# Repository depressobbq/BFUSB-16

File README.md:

# BFUSB-16
its a Big effin USB hub, based on off the shelf parts.

The goal here is to have something with easy to source parts, that asre simultaniously as easy to solder by hand as possible. I went with good ol barrel caps, and single stacked usbs. Also I went with crystals at each of the hub chips, despite them being able to run without one, just due to no trusting it to actually do so. the hope here being that with nice big beefy caps and crystals on each hub chip, this thing ought to be stable even fully populated.
If it works as intended, it should be great for people like me who need a million USB's hooked to their PC for sim racing, but it would also be cool to see if it would work as a 16 USB RAID0 (if my numbers are correct your average flashdrive * 16 is the full usb 2 bandwidth)
Any comments / questions, leave them in the issues, and if you want to help improve the design make a pull request. Im usually not far from a keyboard. This PCB should be good to go with either JLCPCB ( my favorite) or PCBWay.

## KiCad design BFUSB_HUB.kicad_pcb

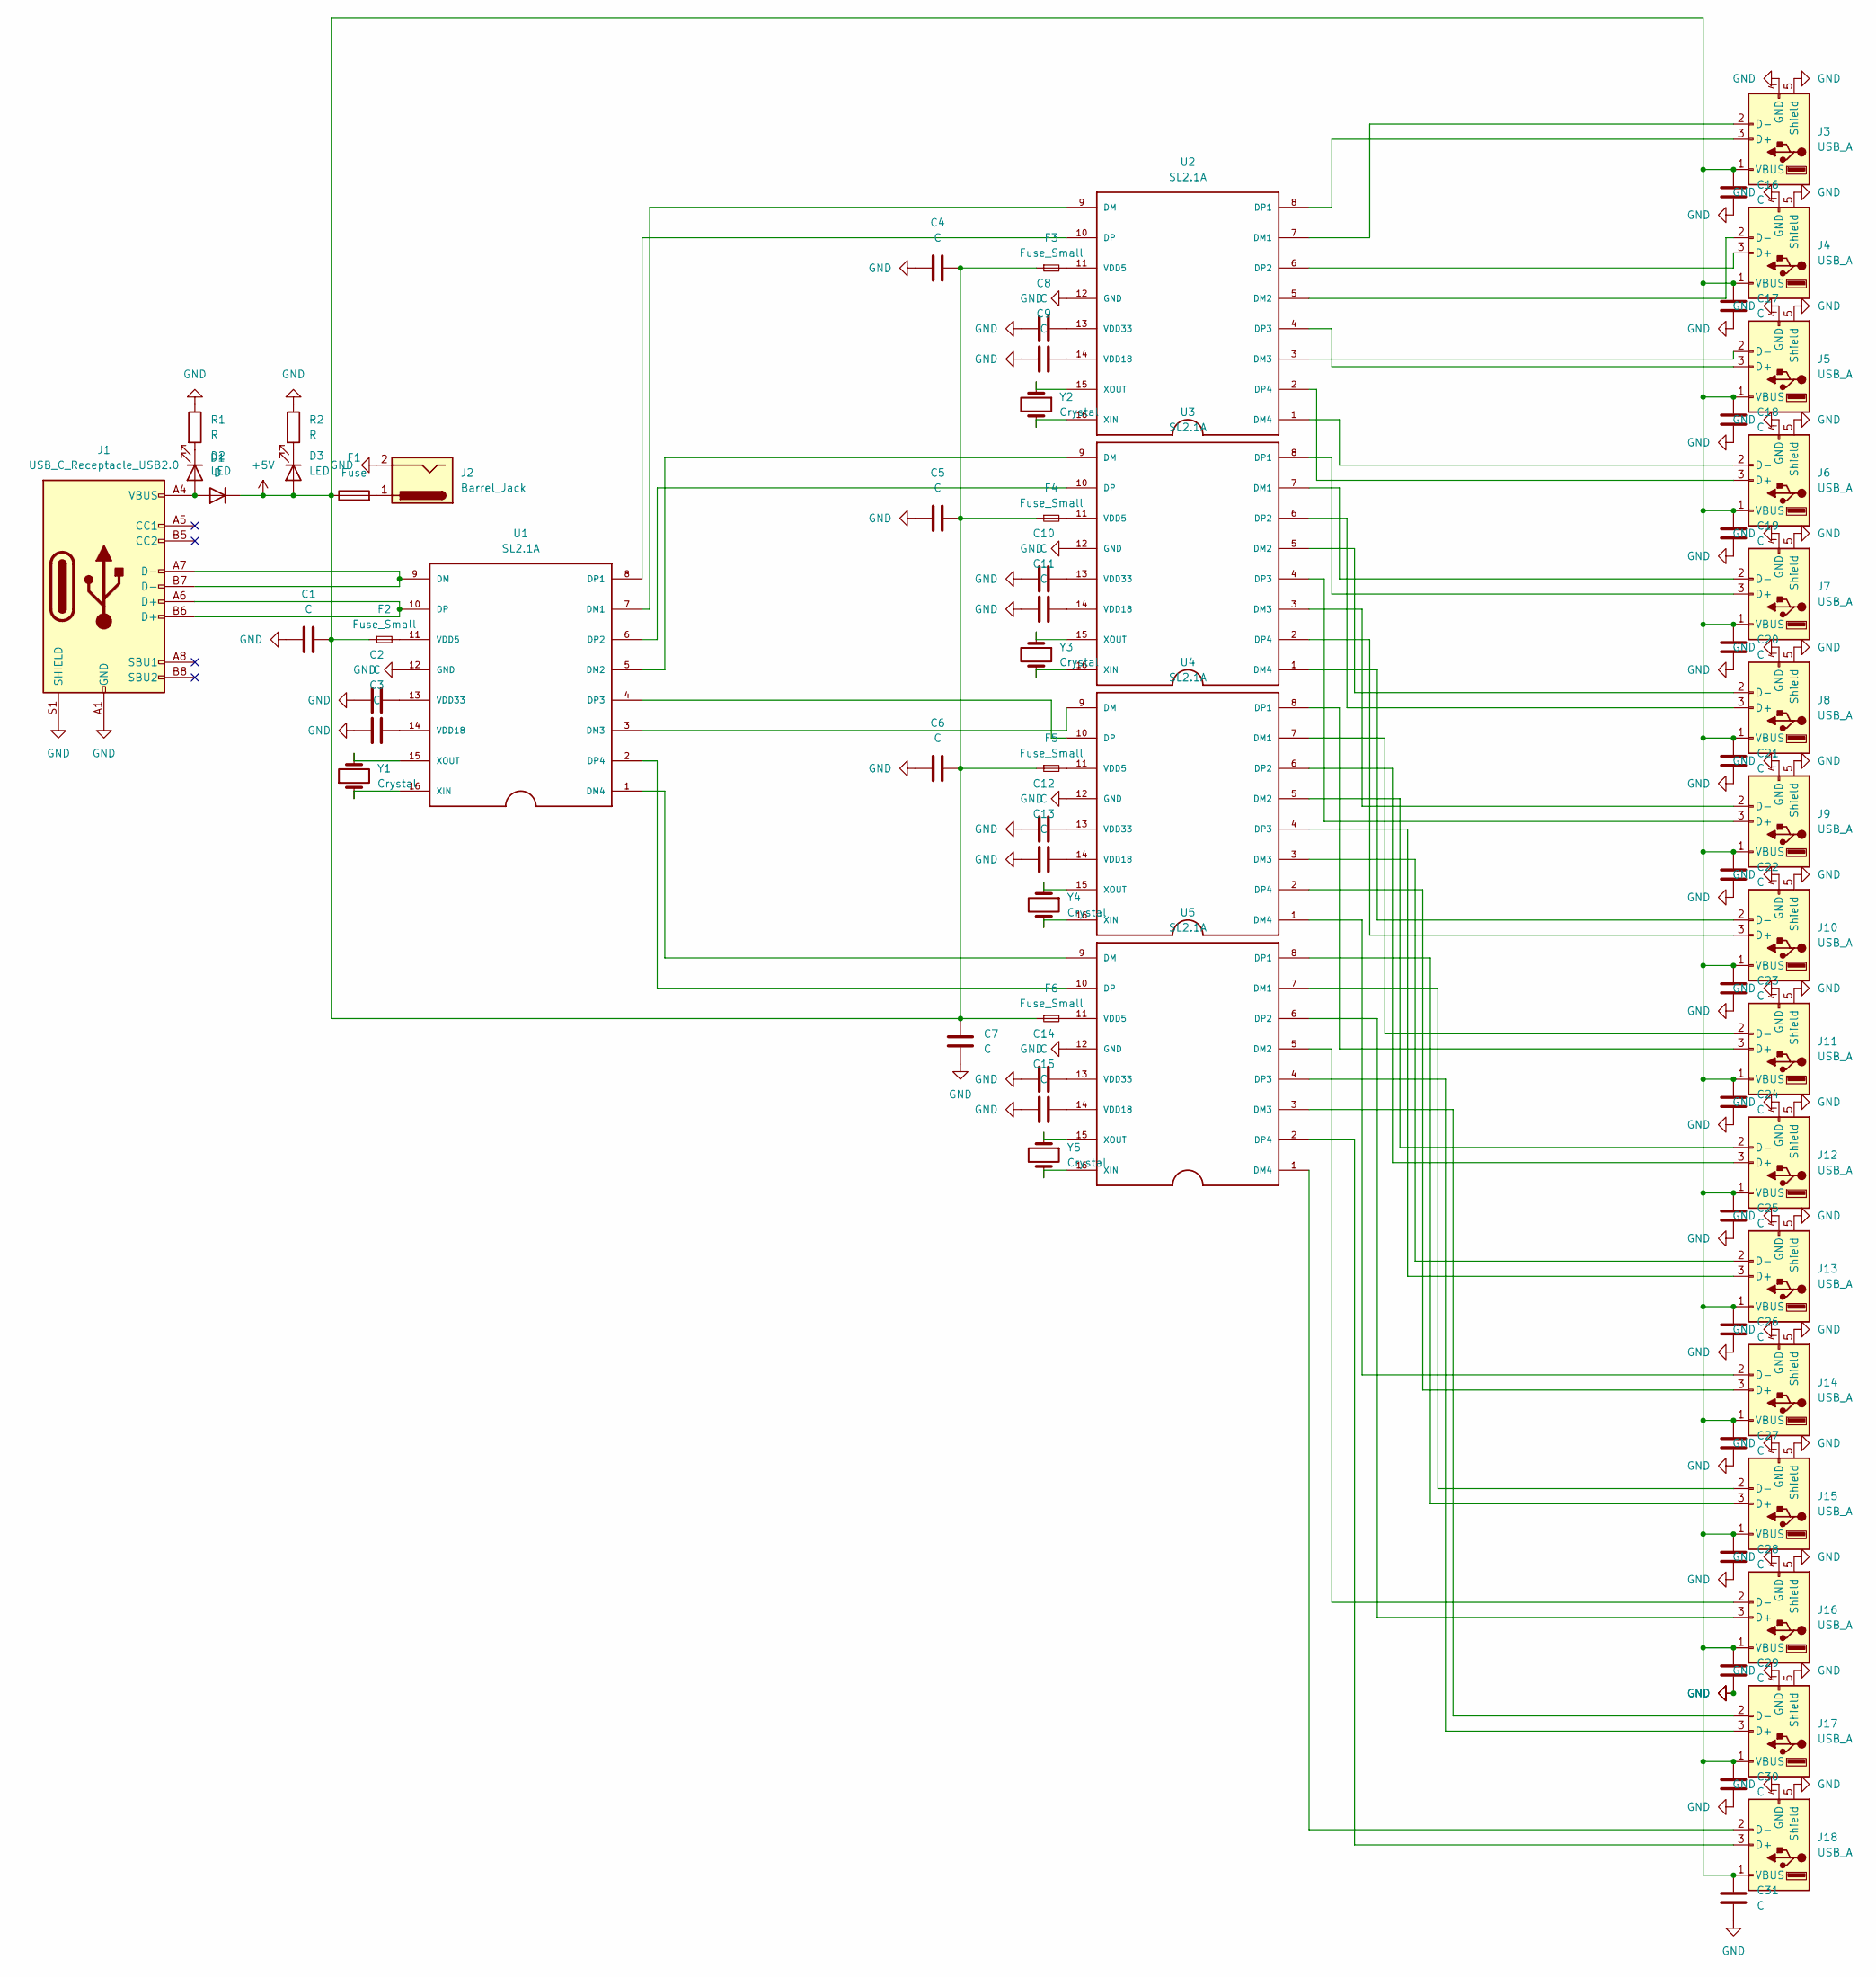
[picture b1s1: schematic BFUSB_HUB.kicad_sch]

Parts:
C1, C2, C3, C4, C5, C6, C7, C8, C9, C10, C11, C12, C13, C14, C15, C16, C17, C18, C19, C20, C21, C22, C23, C24, C25, C26, C27, C28, C29, C30, C31: C; C_Radial_D10.0mm_H12.5mm_P5.00mm
D1: D; D_DO-41_SOD81_P10.16mm_Horizontal
D2, D3: LED; LED_D3.0mm
F1: Fuse; Fuseholder_Cylinder-5x20mm_Stelvio-Kontek_PTF78_Horizontal_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
F2, F3, F4, F5, F6: Fuse_Small; Fuse_2920_7451Metric_Pad2.10x5.45mm_HandSolder
J1: USB_C_Receptacle_USB2.0; USB_C_Receptacle_HRO_TYPE-C-31-M-12
J2: Barrel_Jack; BarrelJack_CUI_PJ-063AH_Horizontal
J3, J4, J5, J6, J7, J8, J9, J10, J11, J12, J13, J14, J15, J16, J17, J18: USB_A; USB_A_Stewart_SS-52100-001_Horizontal
R1, R2: R; R_Axial_DIN0204_L3.6mm_D1.6mm_P1.90mm_Vertical
U1, U2, U3, U4, U5: SL2.1A; SO16
Y1, Y2, Y3, Y4, Y5: Crystal; Crystal_HC49-U_Vertical

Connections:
+5V: C1.2, C4.2, C5.2, C6.2, C7.2, C16.1, C17.1, C18.1, C19.1, C20.1, C21.1, C22.1, C23.1, C24.1, C25.1, C26.1, C27.1, C28.1, C29.1, C30.1, C31.1, D1.1 (K), D3.2 (A), F1.1, F2.1, F3.1, F4.1, F5.1, F6.1, J3.1 (VBUS), J4.1 (VBUS), J5.1 (VBUS), J6.1 (VBUS), J7.1 (VBUS), J8.1 (VBUS), J9.1 (VBUS), J10.1 (VBUS), J11.1 (VBUS), J12.1 (VBUS), J13.1 (VBUS), J14.1 (VBUS), J15.1 (VBUS), J16.1 (VBUS), J17.1 (VBUS), J18.1 (VBUS)
GND: C1.1, C2.1, C3.1, C4.1, C5.1, C6.1, C7.1, C8.1, C9.1, C10.1, C11.1, C12.1, C13.1, C14.1, C15.1, C16.2, C17.2, C18.2, C19.2, C20.2, C21.2, C22.2, C23.2, C24.2, C25.2, C26.2, C27.2, C28.2, C29.2, C30.2, C31.2, J1.A1 (GND), J1.A12 (GND), J1.B1 (GND), J1.B12 (GND), J1.S1 (SHIELD), J2.2, J3.4 (GND), J3.5 (Shield), J4.4 (GND), J4.5 (Shield), J5.4 (GND), J5.5 (Shield), J6.4 (GND), J6.5 (Shield), J7.4 (GND), J7.5 (Shield), J8.4 (GND), J8.5 (Shield), J9.4 (GND), J9.5 (Shield), J10.4 (GND), J10.5 (Shield), J11.4 (GND), J11.5 (Shield), J12.4 (GND), J12.5 (Shield), J13.4 (GND), J13.5 (Shield), J14.4 (GND), J14.5 (Shield), J15.4 (GND), J15.5 (Shield), J16.4 (GND), J16.5 (Shield), J17.4 (GND), J17.5 (Shield), J18.4 (GND), J18.5 (Shield), R1.1, R2.1, U1.12 (GND), U2.12 (GND), U3.12 (GND), U4.12 (GND), U5.12 (GND)
unnamed: C2.2, U1.13 (VDD33)
unnamed: C3.2, U1.14 (VDD18)
unnamed: C8.2, U2.13 (VDD33)
unnamed: C9.2, U2.14 (VDD18)
unnamed: C10.2, U3.13 (VDD33)
unnamed: C11.2, U3.14 (VDD18)
unnamed: C12.2, U4.13 (VDD33)
unnamed: C13.2, U4.14 (VDD18)
unnamed: C14.2, U5.13 (VDD33)
unnamed: C15.2, U5.14 (VDD18)
unnamed: D1.2 (A), D2.2 (A), J1.A4 (VBUS), J1.A9 (VBUS), J1.B4 (VBUS), J1.B9 (VBUS)
unnamed: D2.1 (K), R1.2
unnamed: D3.1 (K), R2.2
unnamed: F1.2, J2.1
unnamed: F2.2, U1.11 (VDD5)
unnamed: F3.2, U2.11 (VDD5)
unnamed: F4.2, U3.11 (VDD5)
unnamed: F5.2, U4.11 (VDD5)
unnamed: F6.2, U5.11 (VDD5)
unnamed: J1.A6 (D+), J1.B6 (D+), U1.10 (DP)
unnamed: J1.A7 (D-), J1.B7 (D-), U1.9 (DM)
unnamed: J3.2 (D-), U2.7 (DM1)
unnamed: J3.3 (D+), U2.8 (DP1)
unnamed: J4.2 (D-), U2.5 (DM2)
unnamed: J4.3 (D+), U2.6 (DP2)
unnamed: J5.2 (D-), U2.3 (DM3)
unnamed: J5.3 (D+), U2.4 (DP3)
unnamed: J6.2 (D-), U2.1 (DM4)
unnamed: J6.3 (D+), U2.2 (DP4)
unnamed: J7.2 (D-), U3.7 (DM1)
unnamed: J7.3 (D+), U3.8 (DP1)
unnamed: J8.2 (D-), U3.5 (DM2)
unnamed: J8.3 (D+), U3.6 (DP2)
unnamed: J9.2 (D-), U3.3 (DM3)
unnamed: J9.3 (D+), U3.4 (DP3)
unnamed: J10.2 (D-), U3.1 (DM4)
unnamed: J10.3 (D+), U3.2 (DP4)
unnamed: J11.2 (D-), U4.7 (DM1)
unnamed: J11.3 (D+), U4.8 (DP1)
unnamed: J12.2 (D-), U4.5 (DM2)
unnamed: J12.3 (D+), U4.6 (DP2)
unnamed: J13.2 (D-), U4.3 (DM3)
unnamed: J13.3 (D+), U4.4 (DP3)
unnamed: J14.2 (D-), U4.1 (DM4)
unnamed: J14.3 (D+), U4.2 (DP4)
unnamed: J15.2 (D-), U5.7 (DM1)
unnamed: J15.3 (D+), U5.8 (DP1)
unnamed: J16.2 (D-), U5.5 (DM2)
unnamed: J16.3 (D+), U5.6 (DP2)
unnamed: J17.2 (D-), U5.3 (DM3)
unnamed: J17.3 (D+), U5.4 (DP3)
unnamed: J18.2 (D-), U5.1 (DM4)
unnamed: J18.3 (D+), U5.2 (DP4)
unnamed: U1.1 (DM4), U5.9 (DM)
unnamed: U1.2 (DP4), U5.10 (DP)
unnamed: U1.3 (DM3), U4.9 (DM)
unnamed: U1.4 (DP3), U4.10 (DP)
unnamed: U1.5 (DM2), U3.9 (DM)
unnamed: U1.6 (DP2), U3.10 (DP)
unnamed: U1.7 (DM1), U2.9 (DM)
unnamed: U1.8 (DP1), U2.10 (DP)
unnamed: U1.15 (XOUT), Y1.2
unnamed: U1.16 (XIN), Y1.1
unnamed: U2.15 (XOUT), Y2.1
unnamed: U2.16 (XIN), Y2.2
unnamed: U3.15 (XOUT), Y3.1
unnamed: U3.16 (XIN), Y3.2
unnamed: U4.15 (XOUT), Y4.1
unnamed: U4.16 (XIN), Y4.2
unnamed: U5.15 (XOUT), Y5.1
unnamed: U5.16 (XIN), Y5.2

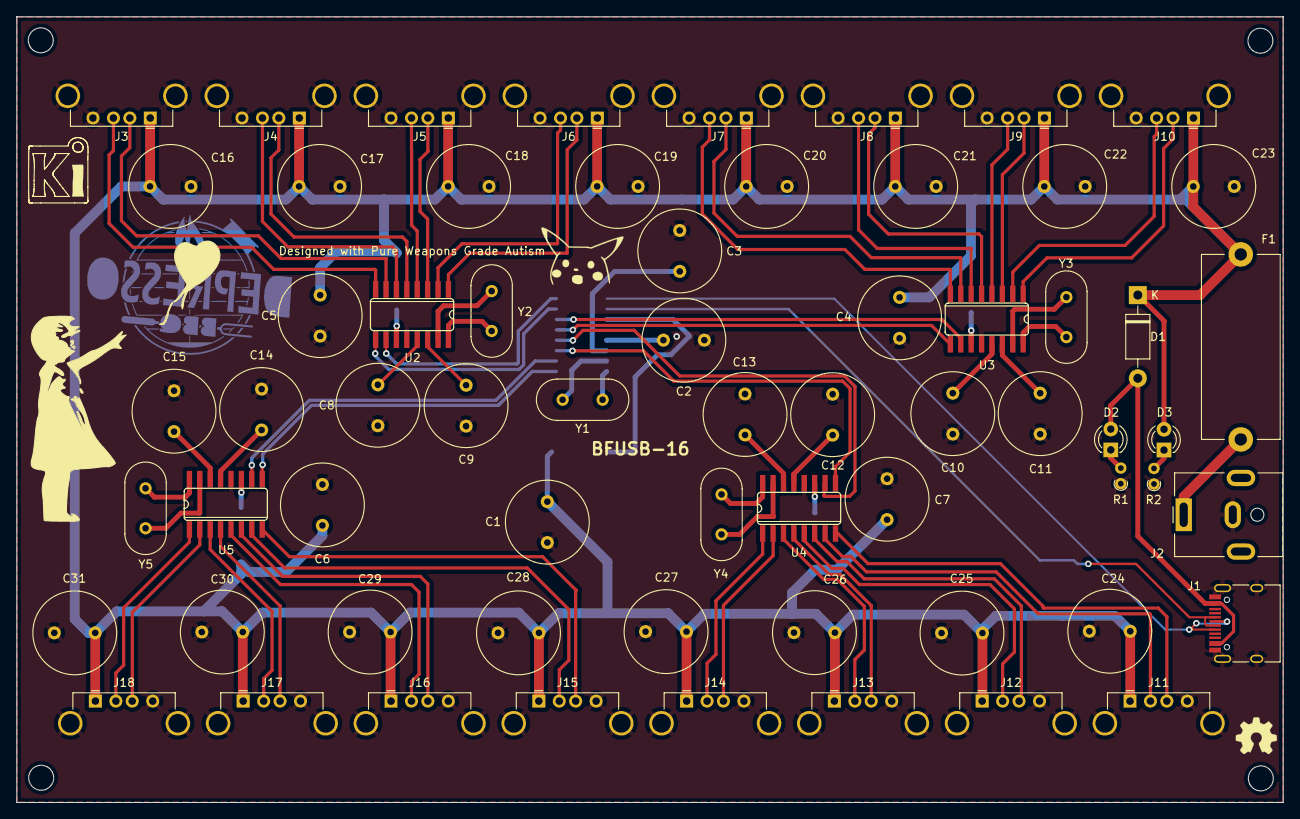
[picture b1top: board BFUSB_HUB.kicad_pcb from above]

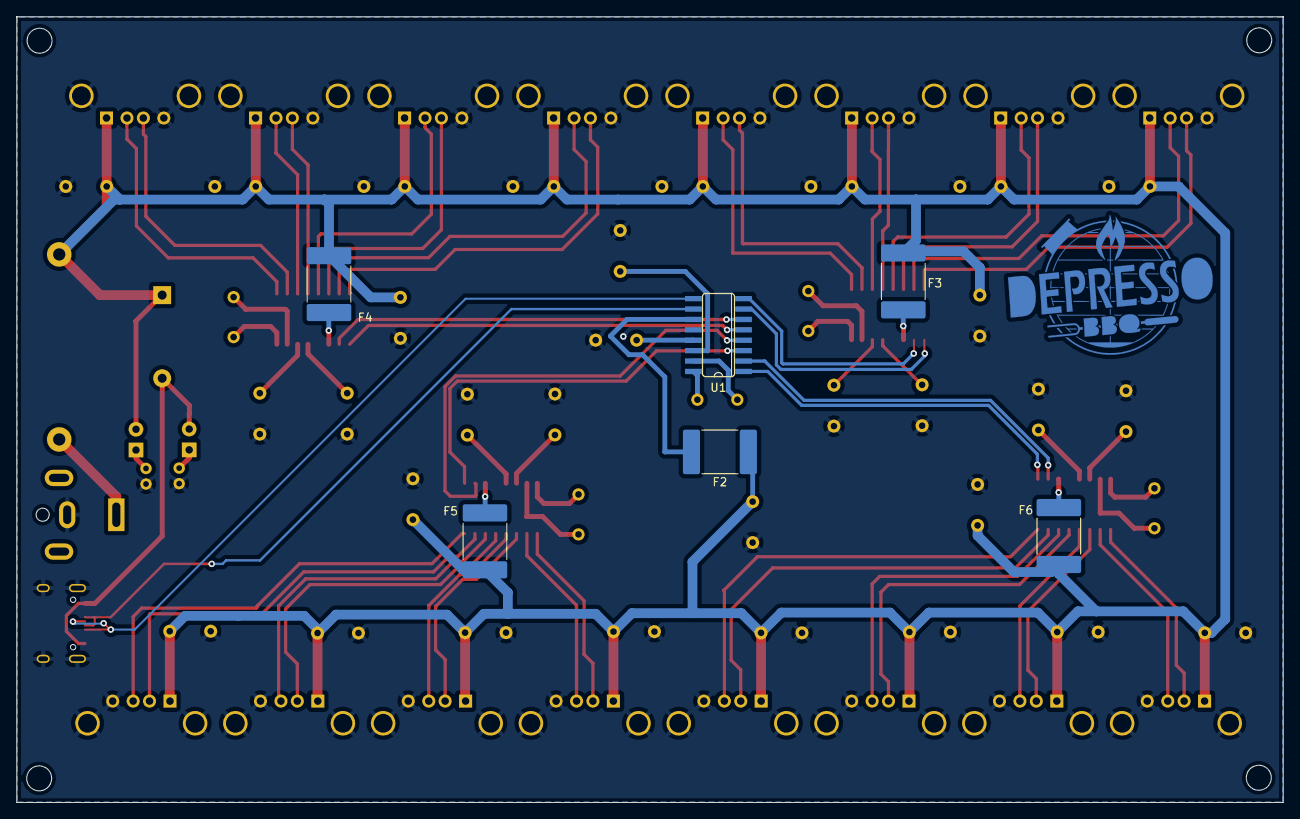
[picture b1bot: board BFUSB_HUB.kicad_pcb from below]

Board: 2 copper layers, 154.7 x 96.0 mm, 70 parts (6 on the bottom side), 73 nets.

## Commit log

2023-04-29 Update README.md
    added pictures of board
2023-04-29 added silksreen model number to board
2023-04-29 Update README.md
    typo fix
